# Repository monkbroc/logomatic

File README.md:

# Logomatic

A gorgeous internet-connected animated logo.

### [Read a writeup about the project](writeup.md) (work in progress)

## Parts

Hardware: PCB, bill of materials

Firmware: software to read animated GIFs and control the LEDs.

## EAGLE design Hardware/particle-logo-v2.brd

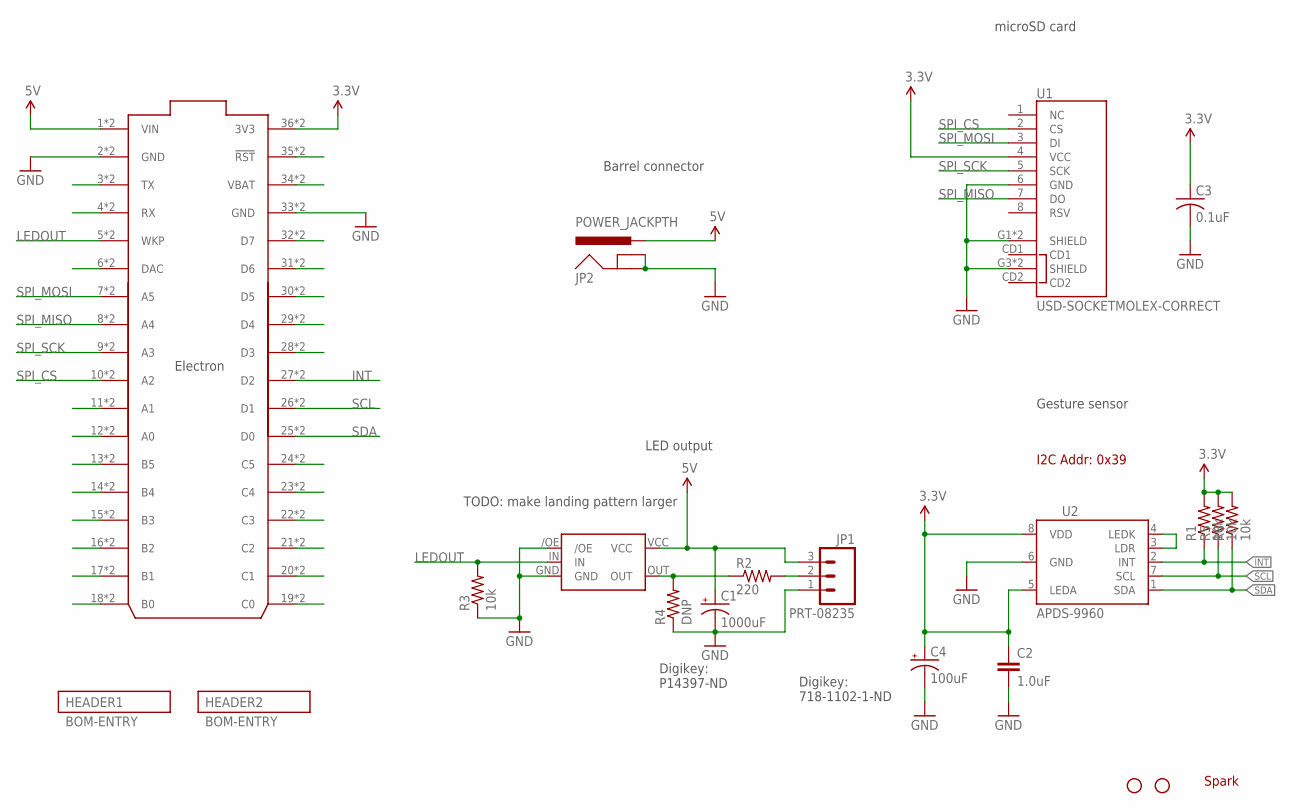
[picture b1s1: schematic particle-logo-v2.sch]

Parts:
C1: 1000uF; CPOL-8MMX20MM-FLAT-MIR; PARTNO EEU-FR1C102L
C2: 1.0uF; 0603-CAP; PARTNO 0603YD105KAT2A
C3: 0.1uF; C0603; PARTNO CC0603JRX7R7BB104
C4: 100uF; EIA7343; PARTNO TAJD107K020RNJ
JP1: PRT-08235; SCREWTERMINAL-3.5MM-3
JP2: POWER_JACKPTH; POWER_JACK_PTH
R1, R3, R5, R6: 10k; R0603; PARTNO ERJ-3EKF1002V
R2: 220; R0603; PARTNO ERJ-3GEYJ221V
R4: DNP; R0603
STANDOFF1, STANDOFF2: STAND-OFF
U1: USD-SOCKETMOLEX-CORRECT; MICRO-SD-MOLEX-CORRECT; PARTNO 1040310811
U2: APDS-9960; PARTNO APDS-9960
U3: ELECTRON_WITH_EXTERNAL_HEADERS_NT; ELECTRON_EXTERNAL_NT
U4: NL17SZ125SOT553; SOT-553; PARTNO NL17SZ125DTT1G
U$1: SPARK_LOGO2

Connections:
3.3V: C2.1, C3.1, C4.A (+), R1.2, R5.2, R6.2, U1.4 (VCC), U2.5 (LEDA), U2.8 (VDD), U3.36 (3V3), U3.@36 (3V3)
5V: C1.2 (+), JP1.3, JP2.PWR, U3.1 (VIN), U3.@1 (VIN), U4.VCC
GND: C1.1 (-), C2.2, C3.2, C4.C (-), JP1.1, JP2.GND, JP2.GNDBREAK, R3.1, R4.1, U1.6 (GND), U1.G1 (SHIELD), U1.G2 (SHIELD), U1.G3 (SHIELD), U1.G4 (SHIELD), U2.6 (GND), U3.2 (GND), U3.33 (GND), U3.@2 (GND), U3.@33 (GND), U4./OE, U4.GND
INT: R1.1, U2.2 (INT), U3.27 (D2), U3.@27 (D2)
LEDOUT: R3.2, U3.5 (WKP), U3.@5 (WKP), U4.IN
unnamed: R2.1, R4.2, U4.OUT
unnamed: U2.3 (LDR), U2.4 (LEDK)
unnamed: JP1.2, R2.2
unnamed: U3.3 (TX), U3.@3 (TX)
unnamed: U3.4 (RX), U3.@4 (RX)
unnamed: U3.6 (DAC), U3.@6 (DAC)
unnamed: U3.11 (A1), U3.@11 (A1)
unnamed: U3.12 (A0), U3.@12 (A0)
unnamed: U3.13 (B5), U3.@13 (B5)
unnamed: U3.14 (B4), U3.@14 (B4)
unnamed: U3.15 (B3), U3.@15 (B3)
unnamed: U3.16 (B2), U3.@16 (B2)
unnamed: U3.17 (B1), U3.@17 (B1)
unnamed: U3.18 (B0), U3.@18 (B0)
unnamed: U3.19 (C0), U3.@19 (C0)
unnamed: U3.20 (C1), U3.@20 (C1)
unnamed: U3.21 (C2), U3.@21 (C2)
unnamed: U3.22 (C3), U3.@22 (C3)
unnamed: U3.23 (C4), U3.@23 (C4)
unnamed: U3.24 (C5), U3.@24 (C5)
unnamed: U3.28 (D3), U3.@28 (D3)
unnamed: U3.29 (D4), U3.@29 (D4)
unnamed: U3.30 (D5), U3.@30 (D5)
unnamed: U3.31 (D6), U3.@31 (D6)
unnamed: U3.32 (D7), U3.@32 (D7)
unnamed: U3.34 (VBAT), U3.@34 (VBAT)
unnamed: U3.35 (!RST), U3.@35 (!RST)
SCL: R5.1, U2.7 (SCL), U3.26 (D1), U3.@26 (D1)
SDA: R6.1, U2.1 (SDA), U3.25 (D0), U3.@25 (D0)
SPI_CS: U1.2 (CS), U3.10 (A2), U3.@10 (A2)
SPI_MISO: U1.7 (DO), U3.8 (A4), U3.@8 (A4)
SPI_MOSI: U1.3 (DI), U3.7 (A5), U3.@7 (A5)
SPI_SCK: U1.5 (SCK), U3.9 (A3), U3.@9 (A3)

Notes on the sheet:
I2C Addr: 0x39
Gesture sensor
microSD card
Barrel connector
LED output
Digikey: 718-1102-1-ND
Digikey: P14397-ND
TODO: make landing pattern larger

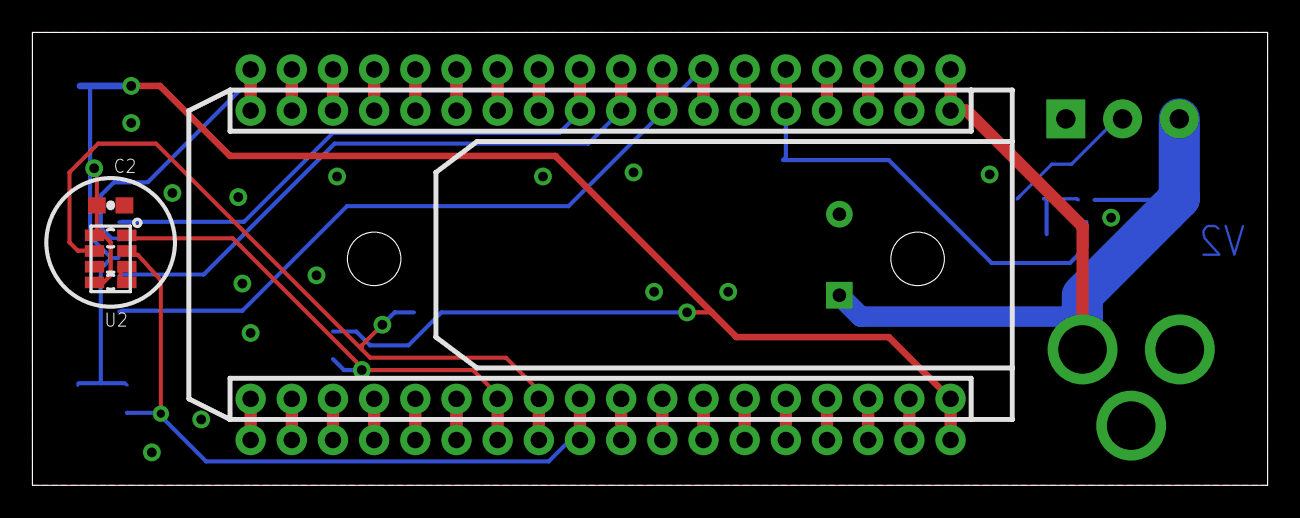
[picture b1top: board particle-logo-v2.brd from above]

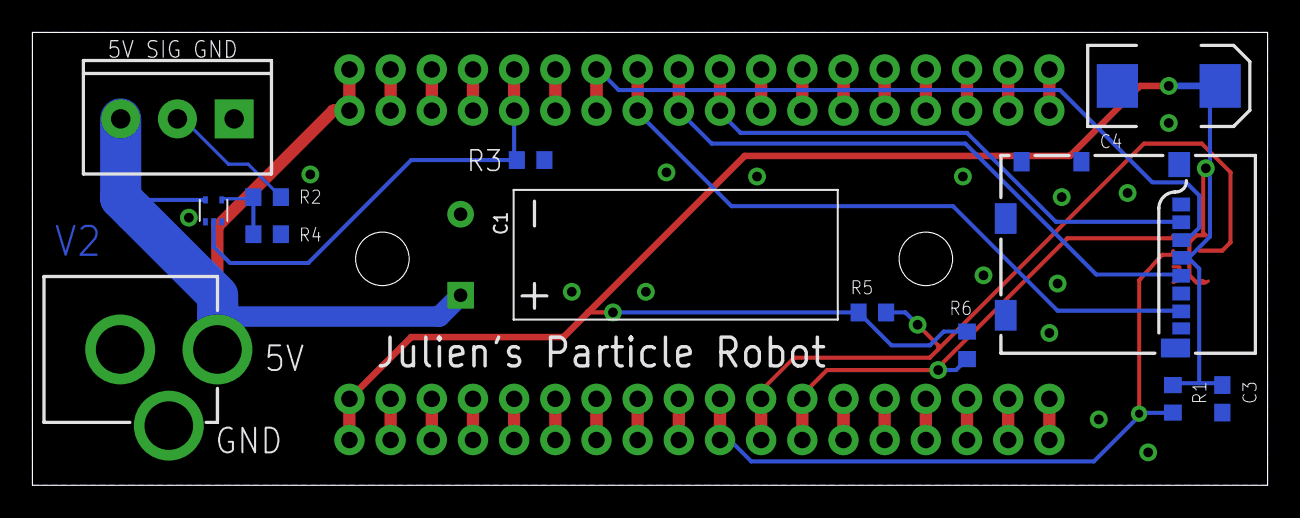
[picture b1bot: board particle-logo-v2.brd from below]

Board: 2 copper layers, 76.2 x 27.9 mm, 19 parts (16 on the bottom side), 38 nets.

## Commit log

2016-06-29 Add BOM and schematics PDF
2016-07-13 Add first implementation of firmware
2016-07-14 Revise board to fix problems in v1
    - missing i2c pull ups
    - missing 3.3v to gesture sensor
    - missing ground to sd card
2016-07-14 Working first version
2016-07-14 Add gesture sensor to firmware
2016-07-29 Update for longer LED strand
2016-07-30 Add animation class
2016-08-02 Wired up the Gif Animation class
2016-08-02 Add the event processing loop
2016-08-04 wireframe
2016-08-04 Demo
2016-08-04 Add off
2016-08-04 Add firworks
2016-08-16 Updates icons
2016-08-16 Finish firmware
2016-08-22 Add animations and mechanical drawings
2016-08-22 Start writeup for Hackster.io
2016-09-20 Add Photos

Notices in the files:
parts and their libraries:
SparkFun-Connectors: Licensing: Creative Commons ShareAlike 4.0 International - https://creativecommons.org/licenses/by-sa/4.0
bom: Copyright (C) 2010, Bob Starr
